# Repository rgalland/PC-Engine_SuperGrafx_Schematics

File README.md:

# PC-Engine_SuperGrafx_Schematics
PC-Engine SuperGrafx Schematics - Reversed Enginnered from actual PCB

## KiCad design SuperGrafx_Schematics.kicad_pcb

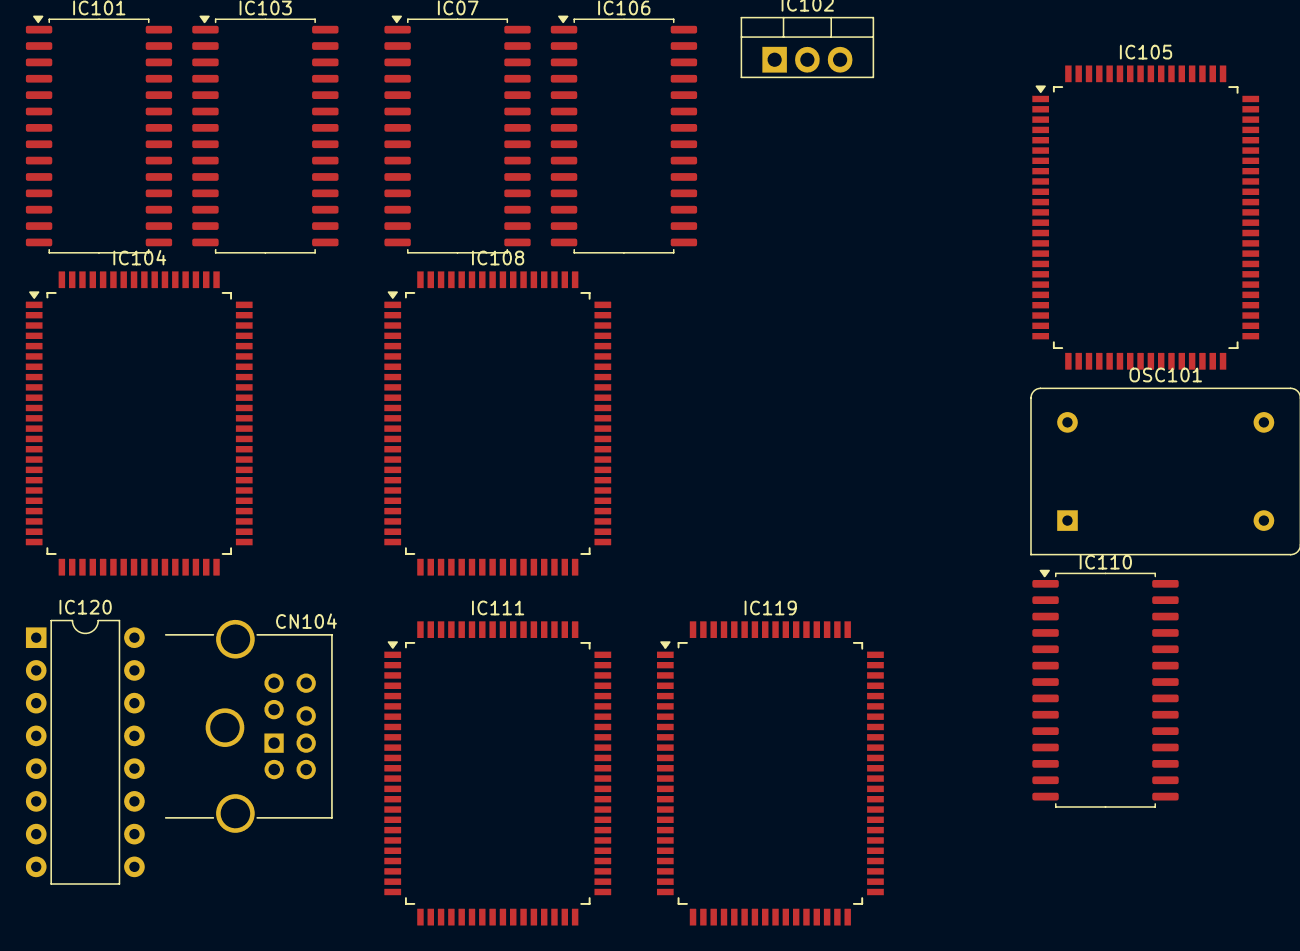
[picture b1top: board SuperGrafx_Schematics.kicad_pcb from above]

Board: 2 copper layers, 14 parts (0 on the bottom side), 153 nets, no tracks yet.

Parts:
CN104: Mini-DIN-8; 1658998-1
IC07, IC101, IC103, IC106, IC110: HSRM20256LM; SOIC-28W_7.5x17.9mm_P1.27mm
IC102: LM7805_TO220; TO-220-3_Vertical
IC104, IC108: HuC6270; PQFP-80_14x20mm_P0.8mm
IC105: HuC6202; PQFP-80_14x20mm_P0.8mm
IC111: HuC6280; PQFP-80_14x20mm_P0.8mm
IC119: HuC6260; PQFP-80_14x20mm_P0.8mm
IC120: MC74HC157N; CERDIP-16_W7.62mm_SideBrazed
OSC101: VX-8232; Oscillator_DIP-14

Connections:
+5V: IC07.28 (VCC), IC101.28 (VCC), IC102.3 (VO), IC103.28 (VCC), IC104.18 (VDD1), IC104.22 (8/16), IC104.32 (VDD2), IC104.47 (VDD3), IC104.72 (VDD4), IC105.3 (VCC), IC105.13 (VCC), IC105.22 (VCC), IC105.43 (VCC), IC105.62 (VCC), IC106.28 (VCC), IC108.18 (VDD1), IC108.22 (8/16), IC108.32 (VDD2), IC108.47 (VDD3), IC108.72 (VDD4), IC110.28 (VCC), IC111.8 (VAA), IC111.15 (VPPD), IC111.19 (VPPA), IC111.47 (VDD), IC111.57 (VCC), IC111.76 (VBB), IC119.1 (VCC), IC119.13 (VCC), IC119.16 (VCC), IC119.21 (AVCC), IC119.22 (BRT+), IC119.27 (AVCC), IC119.28 (B-Y-+), IC119.34 (AVCC), IC119.35 (R-Y+), IC119.36 (AVCC), IC119.41 (AVCC), IC119.42 (Y+), IC119.45 (SYN+), IC119.50 (AVCC), IC119.52 (RGB+), IC119.53 (VCC), IC119.54 (VCC), IC119.57 (VCC), IC119.80 (8/16), IC120.16 (VCC)
/CPU_A0: IC105.7 (CPU_A0), IC110.10 (A0), IC111.6 (A0)
/CPU_A1: IC105.6 (CPU_A1), IC110.9 (A1), IC111.5 (A1)
/CPU_A2: IC105.5 (CPU_A2), IC110.8 (A2), IC111.4 (A2)
/CPU_A3: IC105.4 (CPU_A3), IC110.7 (A3), IC111.3 (A3)
/CPU_A4: IC105.1 (CPU_A4), IC110.6 (A4), IC111.2 (A4)
/CPU_A5: IC110.5 (A5), IC111.1 (A5)
/CPU_A6: IC110.4 (A6), IC111.80 (A6)
/CPU_A7: IC110.3 (A7), IC111.79 (A7)
/CPU_A8: IC110.25 (A8), IC111.78 (A8)
/CPU_A9: IC110.24 (A9), IC111.77 (A9)
/CPU_A10: IC110.21 (A10), IC111.74 (A10)
/CPU_A11: IC110.23 (A11), IC111.73 (A11)
/CPU_A12: IC110.2 (A12), IC111.72 (A12)
/CPU_A13: IC110.26 (A13), IC111.71 (A13)
/CPU_A14: IC110.1 (A14), IC111.70 (A14)
/CPU_D0: IC105.14 (CPU_D0), IC110.11 (Q0), IC111.49 (D0)
/CPU_D1: IC105.15 (CPU_D1), IC110.12 (Q1), IC111.50 (D1)
/CPU_D2: IC105.16 (CPU_D2), IC110.13 (Q2), IC111.51 (D2)
/CPU_D3: IC105.17 (CPU_D3), IC110.15 (Q3), IC111.52 (D3)
/CPU_D4: IC105.18 (CPU_D4), IC110.16 (Q4), IC111.53 (D4)
/CPU_D5: IC105.19 (CPU_D5), IC110.17 (Q5), IC111.54 (D5)
/CPU_D6: IC105.20 (CPU_D6), IC110.18 (Q6), IC111.55 (D6)
/CPU_D7: IC105.21 (CPU_D7), IC110.19 (Q7), IC111.56 (D7)
/CPU_SYNC: IC105.12 (CPU_SYNC), IC111.46 (SYNC)
/DOTCK: IC104.25 (VSYN), IC105.30 (~HSYNC), IC108.25 (VSYN), IC119.71 (HSYN)
/HSYNC: IC104.23 (CK), IC105.28 (DOTCK), IC108.23 (CK), IC119.73 (CK)
/K0: IC111.22 (K0), IC120.4 (Za)
/K1: IC111.24 (K1), IC120.7 (Zb)
/K2: IC111.25 (K2), IC120.9 (Zc)
/K3: IC111.26 (K3), IC120.12 (Zd)
/RDY: IC104.78 (BUSY), IC108.78 (BUSY), IC111.12 (RDY)
/VCE, VIDEO & AUDIO AMPLIFICATION/VD0: IC105.40 (VD0), IC119.62 (VD0)
/VCE, VIDEO & AUDIO AMPLIFICATION/VD1: IC105.39 (VD1), IC119.63 (VD1)
/VCE, VIDEO & AUDIO AMPLIFICATION/VD2: IC105.38 (VD2), IC119.64 (VD2)
/VCE, VIDEO & AUDIO AMPLIFICATION/VD3: IC105.37 (VD3), IC119.65 (VD3)
/VCE, VIDEO & AUDIO AMPLIFICATION/VD4: IC105.36 (VD4), IC119.66 (VD4)
/VCE, VIDEO & AUDIO AMPLIFICATION/VD5: IC105.35 (VD5), IC119.67 (VD5)
/VCE, VIDEO & AUDIO AMPLIFICATION/VD6: IC105.34 (VD6), IC119.68 (VD6)
/VCE, VIDEO & AUDIO AMPLIFICATION/VD7: IC105.33 (VD7), IC119.69 (VD7)
/VCE, VIDEO & AUDIO AMPLIFICATION/VD8: IC105.32 (VD8), IC119.70 (VD8)
/VDC1/MA0: IC101.10 (A0), IC103.10 (A0), IC104.59 (MA0)
/VDC1/MA1: IC101.9 (A1), IC103.9 (A1), IC104.60 (MA1)
/VDC1/MA2: IC101.8 (A2), IC103.8 (A2), IC104.61 (MA2)
/VDC1/MA3: IC101.7 (A3), IC103.7 (A3), IC104.62 (MA3)
/VDC1/MA4: IC101.6 (A4), IC103.6 (A4), IC104.63 (MA4)
/VDC1/MA5: IC101.5 (A5), IC103.5 (A5), IC104.64 (MA5)
/VDC1/MA6: IC101.4 (A6), IC103.4 (A6), IC104.65 (MA6)
/VDC1/MA7: IC101.3 (A7), IC103.3 (A7), IC104.66 (MA7)
/VDC1/MA8: IC101.25 (A8), IC103.25 (A8), IC104.67 (MA8)
/VDC1/MA9: IC101.24 (A9), IC103.24 (A9), IC104.68 (MA9)
/VDC1/MA10: IC101.21 (A10), IC103.21 (A10), IC104.69 (MA10)
/VDC1/MA11: IC101.23 (A11), IC103.23 (A11), IC104.70 (MA11)
/VDC1/MA12: IC101.2 (A12), IC103.2 (A12), IC104.73 (MA12)
/VDC1/MA13: IC101.26 (A13), IC103.26 (A13), IC104.74 (MA13)
/VDC1/MA14: IC101.1 (A14), IC103.1 (A14), IC104.75 (MA14)
/VDC1/MD0: IC103.11 (Q0), IC104.41 (MD0)
/VDC1/MD1: IC103.12 (Q1), IC104.42 (MD1)
/VDC1/MD2: IC103.13 (Q2), IC104.43 (MD2)
/VDC1/MD3: IC103.15 (Q3), IC104.44 (MD3)
/VDC1/MD4: IC103.16 (Q4), IC104.45 (MD4)
/VDC1/MD5: IC103.17 (Q5), IC104.46 (MD5)
/VDC1/MD6: IC103.18 (Q6), IC104.48 (MD6)
/VDC1/MD7: IC103.19 (Q7), IC104.49 (MD7)
/VDC1/MD8: IC101.11 (Q0), IC104.50 (MD8)
/VDC1/MD9: IC101.12 (Q1), IC104.51 (MD9)
/VDC1/MD10: IC101.13 (Q2), IC104.52 (MD10)
/VDC1/MD11: IC101.15 (Q3), IC104.53 (MD11)
/VDC1/MD12: IC101.16 (Q4), IC104.54 (MD12)
/VDC1/MD13: IC101.17 (Q5), IC104.56 (MD13)
/VDC1/MD14: IC101.18 (Q6), IC104.57 (MD14)
/VDC1/MD15: IC101.19 (Q7), IC104.58 (MD15)
/VDC1/V1D0: IC104.38 (VD0), IC105.46 (V1D0)
/VDC1/V1D1: IC104.37 (VD1), IC105.47 (V1D1)
/VDC1/V1D2: IC104.36 (VD2), IC105.48 (V1D2)
/VDC1/V1D3: IC104.35 (VD3), IC105.49 (V1D3)
/VDC1/V1D4: IC104.34 (VD4), IC105.50 (V1D4)
/VDC1/V1D5: IC104.31 (VD5), IC105.51 (V1D5)
/VDC1/V1D6: IC104.30 (VD6), IC105.52 (V1D6)
/VDC1/V1D7: IC104.29 (VD7), IC105.53 (V1D7)
/VDC1/V1D8: IC104.28 (SPGB), IC105.54 (V1D8)
/VDC2/MA0: IC07.10 (A0), IC106.10 (A0), IC108.59 (MA0)
/VDC2/MA1: IC07.9 (A1), IC106.9 (A1), IC108.60 (MA1)
/VDC2/MA2: IC07.8 (A2), IC106.8 (A2), IC108.61 (MA2)
/VDC2/MA3: IC07.7 (A3), IC106.7 (A3), IC108.62 (MA3)
/VDC2/MA4: IC07.6 (A4), IC106.6 (A4), IC108.63 (MA4)
/VDC2/MA5: IC07.5 (A5), IC106.5 (A5), IC108.64 (MA5)
/VDC2/MA6: IC07.4 (A6), IC106.4 (A6), IC108.65 (MA6)
/VDC2/MA7: IC07.3 (A7), IC106.3 (A7), IC108.66 (MA7)
/VDC2/MA8: IC07.25 (A8), IC106.25 (A8), IC108.67 (MA8)
/VDC2/MA9: IC07.24 (A9), IC106.24 (A9), IC108.68 (MA9)
/VDC2/MA10: IC07.21 (A10), IC106.21 (A10), IC108.69 (MA10)
/VDC2/MA11: IC07.23 (A11), IC106.23 (A11), IC108.70 (MA11)
/VDC2/MA12: IC07.2 (A12), IC106.2 (A12), IC108.73 (MA12)
/VDC2/MA13: IC07.26 (A13), IC106.26 (A13), IC108.74 (MA13)
/VDC2/MA14: IC07.1 (A14), IC106.1 (A14), IC108.75 (MA14)
/VDC2/MD0: IC07.11 (Q0), IC108.41 (MD0)
/VDC2/MD1: IC07.12 (Q1), IC108.42 (MD1)
/VDC2/MD2: IC07.13 (Q2), IC108.43 (MD2)
/VDC2/MD3: IC07.15 (Q3), IC108.44 (MD3)
/VDC2/MD4: IC07.16 (Q4), IC108.45 (MD4)
/VDC2/MD5: IC07.17 (Q5), IC108.46 (MD5)
/VDC2/MD6: IC07.18 (Q6), IC108.48 (MD6)
/VDC2/MD7: IC07.19 (Q7), IC108.49 (MD7)
/VDC2/MD8: IC106.11 (Q0), IC108.50 (MD8)
/VDC2/MD9: IC106.12 (Q1), IC108.51 (MD9)
/VDC2/MD10: IC106.13 (Q2), IC108.52 (MD10)
/VDC2/MD11: IC106.15 (Q3), IC108.53 (MD11)
/VDC2/MD12: IC106.16 (Q4), IC108.54 (MD12)
/VDC2/MD13: IC106.17 (Q5), IC108.56 (MD13)
/VDC2/MD14: IC106.18 (Q6), IC108.57 (MD14)
/VDC2/MD15: IC106.19 (Q7), IC108.58 (MD15)
/VDC2/V2D0: IC105.57 (V2D0), IC108.38 (VD0)
/VDC2/V2D1: IC105.58 (V2D1), IC108.37 (VD1)
/VDC2/V2D2: IC105.59 (V2D2), IC108.36 (VD2)
/VDC2/V2D3: IC105.60 (V2D3), IC108.35 (VD3)
/VDC2/V2D4: IC105.61 (V2D4), IC108.34 (VD4)
/VDC2/V2D5: IC105.65 (V2D5), IC108.31 (VD5)
/VDC2/V2D6: IC105.66 (V2D6), IC108.30 (VD6)
/VDC2/V2D7: IC105.67 (V2D7), IC108.29 (VD7)
/VDC2/V2D8: IC105.68 (V2D8), IC108.28 (SPGB)
/VPC_A0: IC104.79 (A0), IC105.27 (A0), IC108.79 (A0), IC119.74 (A0)
/VPC_A1: IC104.80 (A1), IC105.26 (A1), IC108.80 (A1), IC119.75 (A1)
/VPC_A2: IC105.25 (A2), IC119.76 (A2)
/VPC_D0: IC104.21 (D0), IC105.71 (D0), IC108.21 (D0), IC119.12 (D0)
/VPC_D1: IC104.20 (D1), IC105.72 (D1), IC108.20 (D1), IC119.11 (D1)
/VPC_D2: IC104.19 (D2), IC105.73 (D2), IC108.19 (D2), IC119.10 (D2)
/VPC_D3: IC104.17 (D3), IC105.74 (D3), IC108.17 (D3), IC119.9 (D3)
/VPC_D4: IC104.16 (D4), IC105.75 (D4), IC108.16 (D4), IC119.8 (D4)
/VPC_D5: IC104.15 (D5), IC105.76 (D5), IC108.15 (D5), IC119.7 (D5)
/VPC_D6: IC104.14 (D6), IC105.77 (D6), IC108.14 (D6), IC119.6 (D6)
/VPC_D7: IC104.13 (D7), IC105.78 (D7), IC108.13 (D7), IC119.5 (D7)
/VSYNC: IC104.26 (HSYN), IC108.26 (HSYN), IC119.72 (VSYN)
/~CPU_RD: IC105.9 (~CPU_RD), IC110.22 (~OE), IC111.62 (RD)
/~CPU_VCD_CS: IC105.10 (~CPU_VCD_CS), IC111.60 (CE7)
/~CPU_VCE_CS: IC105.11 (~CPU_VCE_CS), IC111.59 (CEK)
/~CPU_WR: IC105.8 (~CPU_WR), IC110.27 (~WE), IC111.63 (WR)
/~IRQ1: IC104.77 (IRQ), IC108.77 (IRQ), IC111.44 (IRQ1)
/~RAM_CS: IC110.20 (~CS), IC111.61 (CER)
/~RST: IC104.24 (RST), IC105.80 (~RST), IC108.24 (RST), IC111.11 (RST)
/~VCE_CS: IC105.24 (~VCE_CS), IC119.79 (CS)
/~VDC1_CS: IC104.1 (CS), IC105.55 (~VDC1_CS)
/~VDC2_CS: IC105.56 (~VDC2_CS), IC108.1 (CS)
/~VPC_RD: IC104.3 (RD), IC105.44 (~VPC_RD), IC108.3 (RD), IC119.77 (WR)
/~VPC_WR: IC104.2 (WR), IC105.45 (~VPC_WR), IC108.2 (WR), IC119.78 (RD)
GND: IC07.14 (GND), IC101.14 (GND), IC102.2 (GND), IC103.14 (GND), IC104.11 (VSS1), IC104.33 (VSS2), IC104.55 (VSS3), IC104.71 (VSS4), IC105.2 (GND), IC105.23 (GND), IC105.29 (GND), IC105.31 (GND), IC105.42 (GND), IC105.63 (GND), IC105.70 (GND), IC106.14 (GND), IC108.11 (VSS1), IC108.33 (VSS2), IC108.55 (VSS3), IC108.71 (VSS4), IC110.14 (GND), IC111.7 (VSS1), IC111.16 (VSS5), IC111.21 (VSSA), IC111.48 (VSS4), IC111.58 (VSS3), IC111.75 (VSS2), IC119.3 (GND), IC119.14 (GND), IC119.15 (GND), IC119.19 (AGND), IC119.25 (AGND), IC119.29 (AGND), IC119.32 (AGND), IC119.39 (AGND), IC119.48 (AGND), IC119.55 (GND), IC119.56 (GND), IC120.8 (GND), IC120.15 (E), OSC101.7 (GND)
unnamed: IC07.20 (~CS), IC106.20 (~CS), IC108.76 (MA15)
unnamed: IC07.22 (~OE), IC106.22 (~OE), IC108.40 (MRD)
unnamed: IC07.27 (~WE), IC106.27 (~WE), IC108.39 (MWR)
unnamed: IC101.20 (~CS), IC103.20 (~CS), IC104.76 (MA15)
unnamed: IC101.22 (~OE), IC103.22 (~OE), IC104.40 (MRD)
unnamed: IC101.27 (~WE), IC103.27 (~WE), IC104.39 (MWR)
unnamed: IC119.43 (SYN-), IC119.46 (RGB-)

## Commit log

2024-04-18 Missed out CD dection signal to main CPU and found values of decoupling capacitors under CPU hidden by EMI shield.
2024-04-19 Rev 0.1 commit
2024-04-19 Pdf location moved to output based on revision
